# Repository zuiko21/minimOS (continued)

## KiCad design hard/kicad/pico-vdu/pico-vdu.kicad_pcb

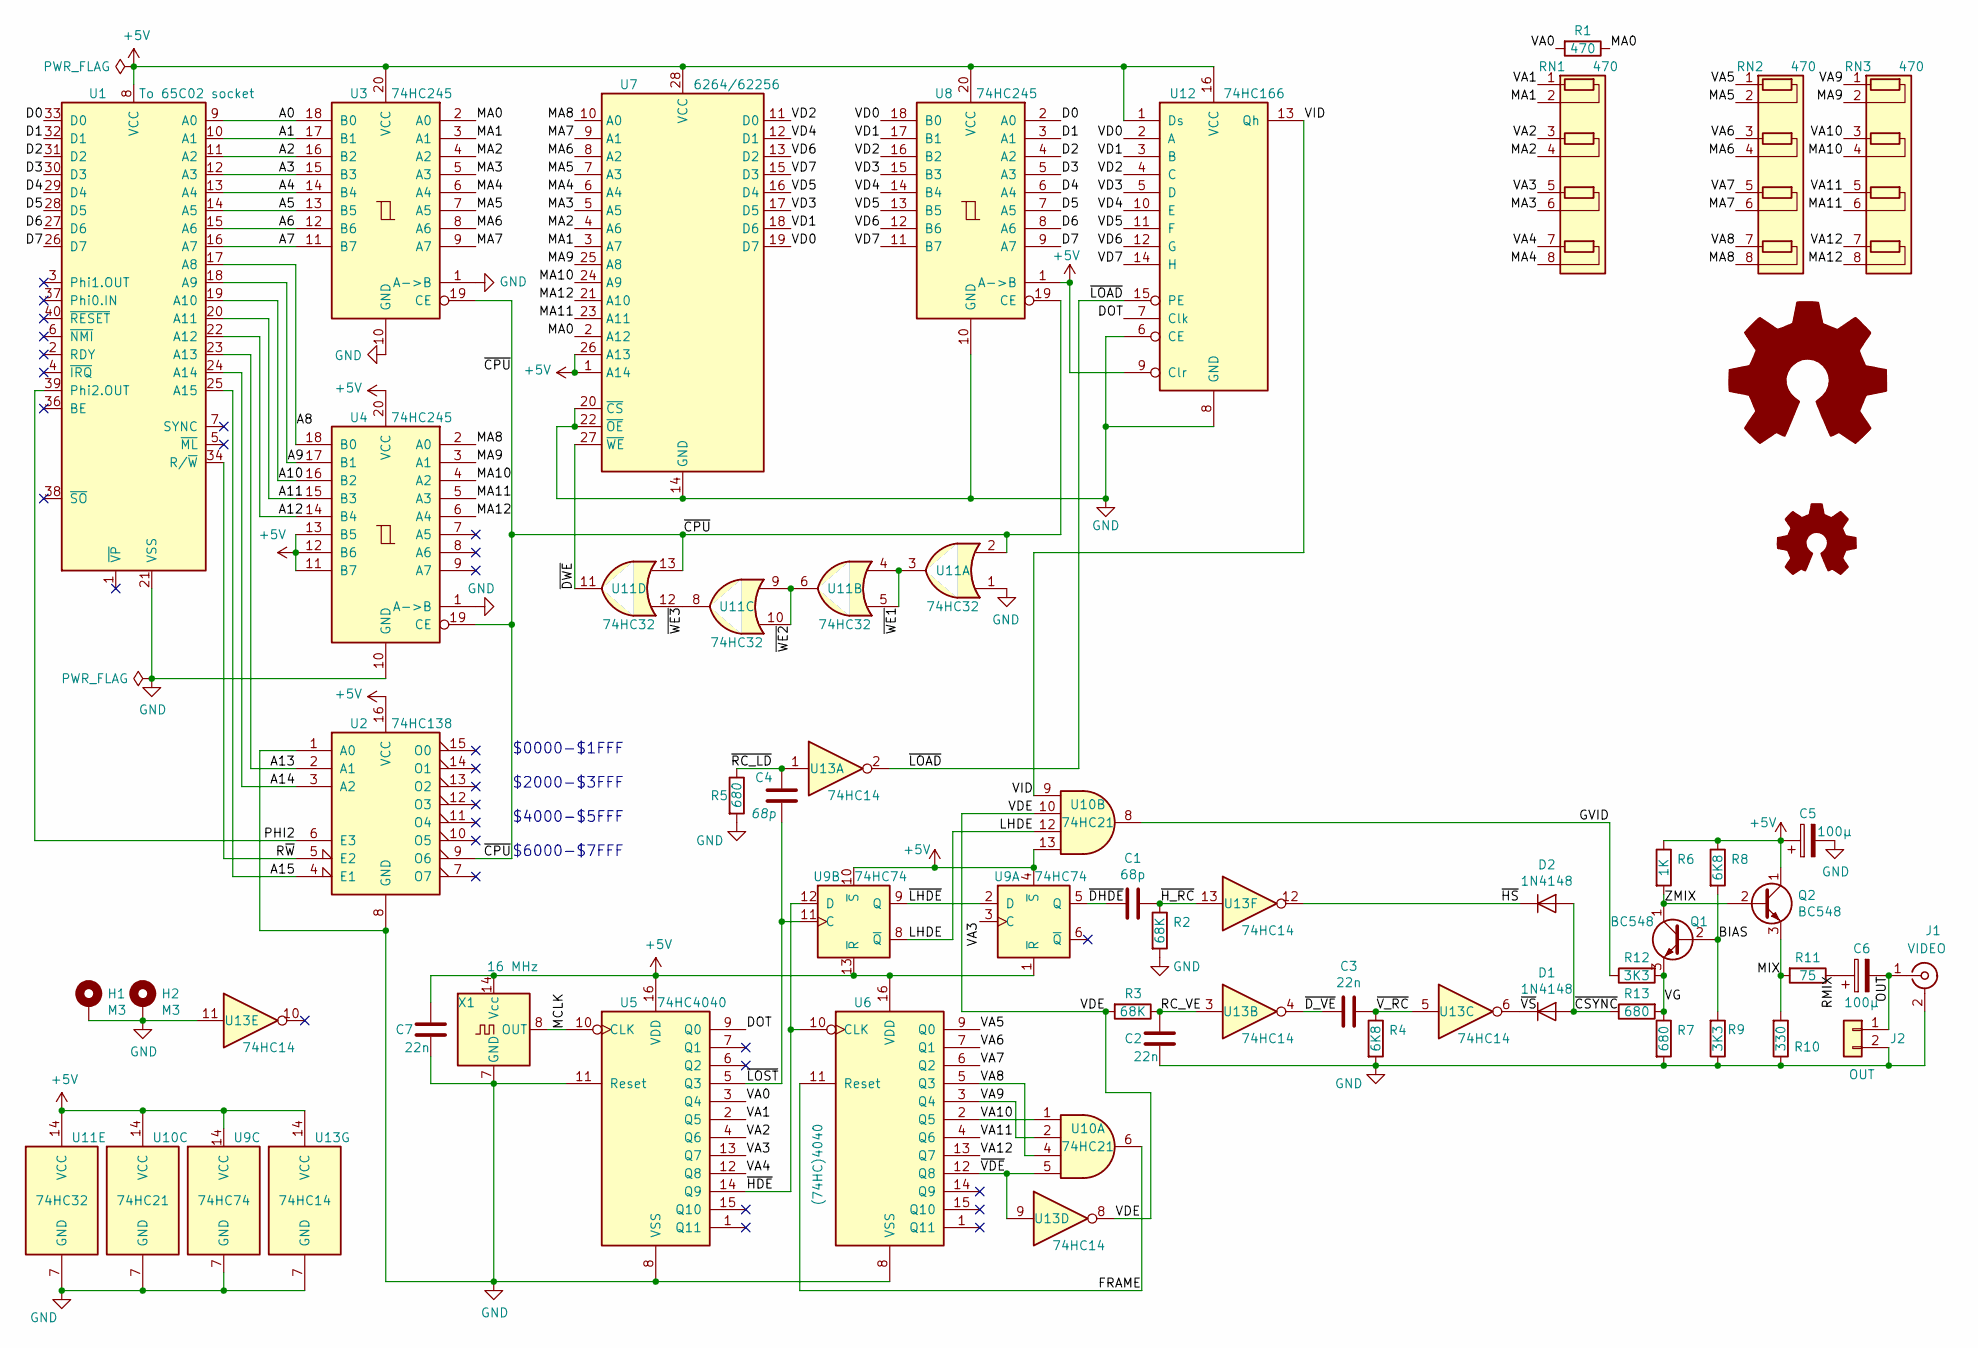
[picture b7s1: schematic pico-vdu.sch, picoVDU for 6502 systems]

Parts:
C1, C4: 68p; C_Disc_D3.8mm_W2.6mm_P2.50mm
C2, C3, C7: 22n; C_Rect_L7.2mm_W2.5mm_P5.00mm_FKS2_FKP2_MKS2_MKP2
C5, C6: 100µ; CP_Radial_D4.0mm_P1.50mm
D1, D2: 1N4148; D_DO-35_SOD27_P2.54mm_Vertical_AnodeUp
H1, H2: M3; MountingHole_3.2mm_M3_DIN965_Pad
J1: VIDEO; 1xRCA
J2: OUT; PinSocket_1x02_P2.54mm_Horizontal
LOGO1: Logo_Open_Hardware_Large; OSHW-Symbol_8.9x8mm_SilkScreen
LOGO2: La Jaquería; jaqueria
Q1, Q2: BC548; TO-92_Inline
R1: 470; R_Axial_DIN0207_L6.3mm_D2.5mm_P2.54mm_Vertical
R2, R3: 68K; R_Axial_DIN0207_L6.3mm_D2.5mm_P2.54mm_Vertical
R4, R8: 6K8; R_Axial_DIN0207_L6.3mm_D2.5mm_P2.54mm_Vertical
R5, R7, R13: 680; R_Axial_DIN0207_L6.3mm_D2.5mm_P2.54mm_Vertical
R6: 1K; R_Axial_DIN0207_L6.3mm_D2.5mm_P2.54mm_Vertical
R9, R12: 3K3; R_Axial_DIN0207_L6.3mm_D2.5mm_P2.54mm_Vertical
R10: 330; R_Axial_DIN0207_L6.3mm_D2.5mm_P2.54mm_Vertical
R11: 75; R_Axial_DIN0207_L6.3mm_D2.5mm_P2.54mm_Vertical
RN1, RN2, RN3: 470; R_Array_SIP8
U1: To 65C02 socket; DIP-40_W15.24mm_Socket
U2: 74HC138; DIP-16_W7.62mm_Socket
U3, U4, U8: 74HC245; DIP-20_W7.62mm_Socket
U5: 74HC4040; DIP-16_W7.62mm_Socket
U6: (74HC)4040; DIP-16_W7.62mm_Socket
U7: 6264/62256; DIP-28_W15.24mm_Socket
U9: 74HC74; DIP-14_W7.62mm_Socket
U10: 74HC21; DIP-14_W7.62mm_Socket
U11: 74HC32; DIP-14_W7.62mm_Socket
U12: 74HC166; DIP-16_W7.62mm_Socket
U13: 74HC14; DIP-14_W7.62mm_Socket
X1: 16 MHz; Oscillator_DIP-14

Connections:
+5V: C5.1, C7.2, Q2.1 (C), R6.1, R8.1, U1.8 (VCC), U2.16 (VCC), U3.20 (VCC), U4.11 (B7), U4.12 (B6), U4.13 (B5), U4.20 (VCC), U5.16 (VDD), U6.16 (VDD), U7.1 (A14), U7.26 (A13), U7.28 (VCC), U8.1 (A->B), U8.20 (VCC), U9.1 (~R), U9.4 (~S), U9.10 (~S), U9.13 (~R), U9.14 (VCC), U10.13, U10.14 (VCC), U11.14 (VCC), U12.1 (Ds), U12.9 (Clr), U12.16 (VCC), U13.14 (VCC), X1.14 (Vcc)
/A0: U1.9 (A0), U3.18 (B0)
/A1: U1.10 (A1), U3.17 (B1)
/A2: U1.11 (A2), U3.16 (B2)
/A3: U1.12 (A3), U3.15 (B3)
/A4: U1.13 (A4), U3.14 (B4)
/A5: U1.14 (A5), U3.13 (B5)
/A6: U1.15 (A6), U3.12 (B6)
/A7: U1.16 (A7), U3.11 (B7)
/A8: U1.17 (A8), U4.18 (B0)
/A9: U1.18 (A9), U4.17 (B1)
/A10: U1.19 (A10), U4.16 (B2)
/A11: U1.20 (A11), U4.15 (B3)
/A12: U1.22 (A12), U4.14 (B4)
/A13: U1.23 (A13), U2.2 (A1)
/A14: U1.24 (A14), U2.3 (A2)
/A15: U1.25 (A15), U2.4 (E1)
/BIAS: Q1.2 (B), R8.2, R9.2
/D0: U1.33 (D0), U8.2 (A0)
/D1: U1.32 (D1), U8.3 (A1)
/D2: U1.31 (D2), U8.4 (A2)
/D3: U1.30 (D3), U8.5 (A3)
/D4: U1.29 (D4), U8.6 (A4)
/D5: U1.28 (D5), U8.7 (A5)
/D6: U1.27 (D6), U8.8 (A6)
/D7: U1.26 (D7), U8.9 (A7)
/DOT: U5.9 (Q0), U12.7 (Clk)
/FRAME: U6.11 (Reset), U10.6
/GVID: R12.1, U10.8
/LHDE: U9.8 (~Q), U10.12
/MA0: R1.1, U3.2 (A0), U7.2 (A12)
/MA1: RN1.2 (R1.2), U3.3 (A1), U7.3 (A7)
/MA2: RN1.4 (R2.2), U3.4 (A2), U7.4 (A6)
/MA3: RN1.6 (R3.2), U3.5 (A3), U7.5 (A5)
/MA4: RN1.8 (R4.2), U3.6 (A4), U7.6 (A4)
/MA5: RN2.2 (R1.2), U3.7 (A5), U7.7 (A3)
/MA6: RN2.4 (R2.2), U3.8 (A6), U7.8 (A2)
/MA7: RN2.6 (R3.2), U3.9 (A7), U7.9 (A1)
/MA8: RN2.8 (R4.2), U4.2 (A0), U7.10 (A0)
/MA9: RN3.2 (R1.2), U4.3 (A1), U7.25 (A8)
/MA10: RN3.4 (R2.2), U4.4 (A2), U7.24 (A9)
/MA11: RN3.6 (R3.2), U4.5 (A3), U7.23 (A11)
/MA12: RN3.8 (R4.2), U4.6 (A4), U7.21 (A10)
/MCLK: U5.10 (CLK), X1.8 (OUT)
/MIX: Q2.3 (E), R10.2, R11.2
/OUT: C6.2, J1.1 (In), J2.1
/PHI2: U1.39 (Phi2.OUT), U2.6 (E3)
/RC_VE: C2.2, R3.1, U13.3
/RMIX: C6.1, R11.1
/R~W: U1.34 (R/~W), U2.5 (E2)
/VA0: R1.2, U5.3 (Q4)
/VA1: RN1.1 (R1.1), U5.2 (Q5)
/VA2: RN1.3 (R2.1), U5.4 (Q6)
/VA3: RN1.5 (R3.1), U5.13 (Q7), U9.3 (C)
/VA4: RN1.7 (R4.1), U5.12 (Q8)
/VA5: RN2.1 (R1.1), U6.9 (Q0)
/VA6: RN2.3 (R2.1), U6.7 (Q1)
/VA7: RN2.5 (R3.1), U6.6 (Q2)
/VA8: RN2.7 (R4.1), U6.5 (Q3), U10.4
/VA9: RN3.1 (R1.1), U6.3 (Q4), U10.2
/VA10: RN3.3 (R2.1), U6.2 (Q5), U10.1
/VA11: RN3.5 (R3.1), U6.4 (Q6)
/VA12: RN3.7 (R4.1), U6.13 (Q7)
/VD0: U7.19 (D7), U8.18 (B0), U12.2 (A)
/VD1: U7.18 (D6), U8.17 (B1), U12.3 (B)
/VD2: U7.11 (D0), U8.16 (B2), U12.4 (C)
/VD3: U7.17 (D5), U8.15 (B3), U12.5 (D)
/VD4: U7.12 (D1), U8.14 (B4), U12.10 (E)
/VD5: U7.16 (D4), U8.13 (B5), U12.11 (F)
/VD6: U7.13 (D2), U8.12 (B6), U12.12 (G)
/VD7: U7.15 (D3), U8.11 (B7), U12.14 (H)
/VDE: R3.2, U10.10, U13.8
/VG: Q1.3 (E), R7.1, R12.2, R13.2
/VID: U10.9, U12.13 (Qh)
/ZMIX: Q1.1 (C), Q2.2 (B), R6.2
/~CPU: U2.9 (O6), U3.19 (CE), U4.19 (CE), U8.19 (CE), U11.2, U11.13
/~CSYNC: D1.2 (A), D2.2 (A), R13.1
/~DHDE: C1.2, U9.5 (Q)
/~DWE: U7.27 (~WE~), U11.11
/~D_VE: C3.2, U13.4
/~HDE: U5.14 (Q9), U6.10 (CLK), U9.12 (D)
/~HS: D2.1 (K), U13.12
/~H_RC: C1.1, R2.1, U13.13
/~LHDE: U9.2 (D), U9.9 (Q)
/~LOAD: U12.15 (PE), U13.2
/~LOST: C4.1, U5.5 (Q3), U9.11 (C)
/~RC_LD: C4.2, R5.1, U13.1
/~VDE: U6.12 (Q8), U10.5, U13.9
/~VS: D1.1 (K), U13.6
/~V_RC: C3.1, R4.1, U13.5
/~WE1: U11.3, U11.4, U11.5
/~WE2: U11.6, U11.9, U11.10
/~WE3: U11.8, U11.12
GND: C2.1, C5.2, C7.1, H1.1, H2.1, J1.2 (Ext), J2.2, R2.2, R4.2, R5.2, R7.2, R9.1, R10.1, U1.21 (VSS), U2.1 (A0), U2.8 (GND), U3.1 (A->B), U3.10 (GND), U4.1 (A->B), U4.10 (GND), U5.8 (VSS), U5.11 (Reset), U6.8 (VSS), U7.14 (GND), U7.20 (~CS), U7.22 (~OE~), U8.10 (GND), U9.7 (GND), U10.7 (GND), U11.1, U11.7 (GND), U12.6 (CE), U12.8 (GND), U13.7 (GND), U13.11, X1.7 (GND)

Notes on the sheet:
$0000-$1FFF $2000-$3FFF $4000-$5FFF $6000-$7FFF

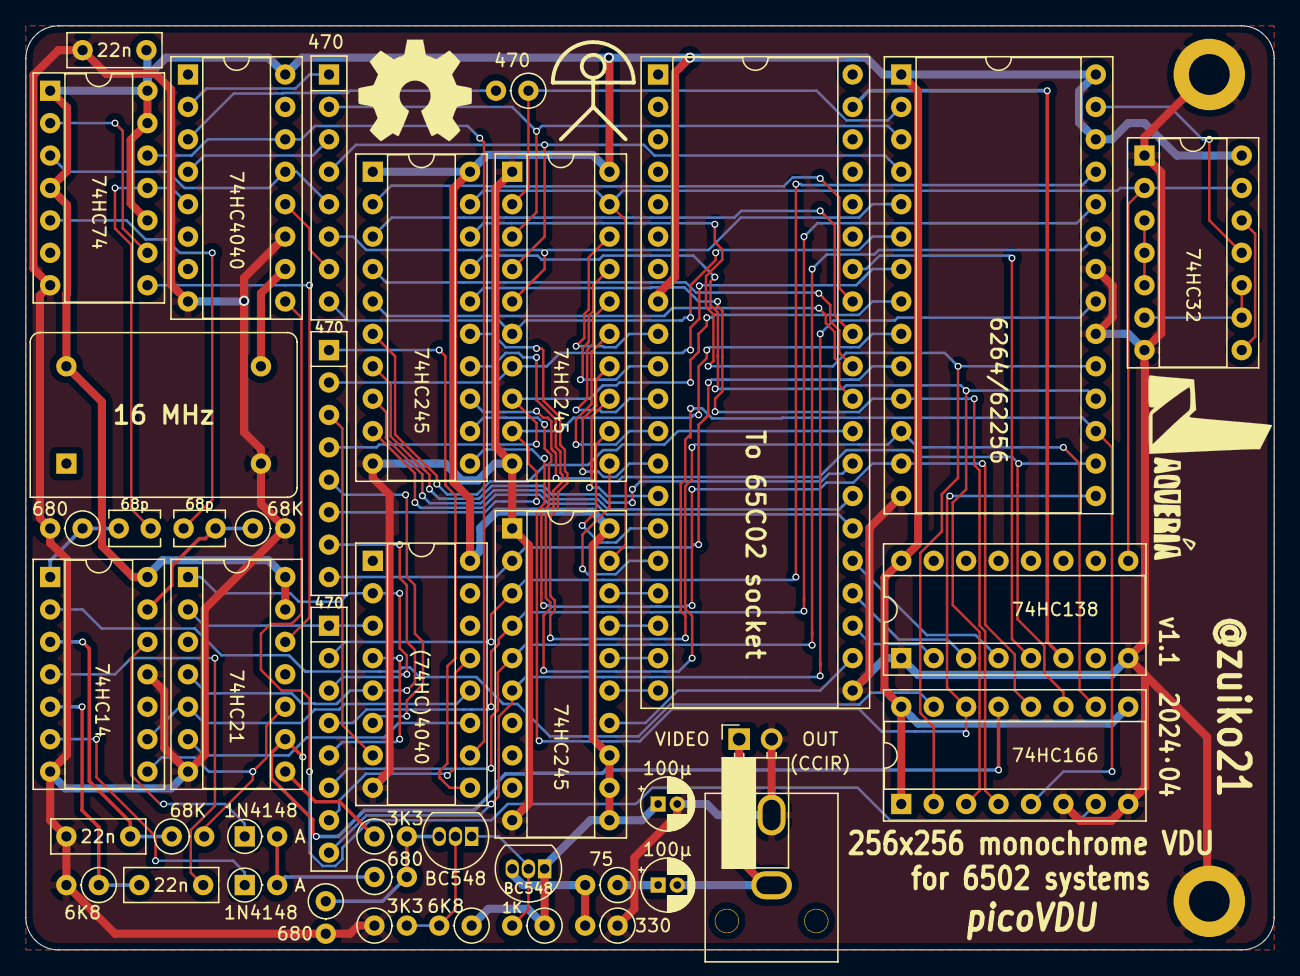
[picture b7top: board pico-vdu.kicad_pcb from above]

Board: 2 copper layers, 97.8 x 72.4 mm, 47 parts (0 on the bottom side), 94 nets.

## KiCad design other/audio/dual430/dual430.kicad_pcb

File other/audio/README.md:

This folder has NOTHING to do with **minimOS**, just a handy location for other 
projects.

*All rights reserved! (C) 2018-2020 Carlos J. Santisteban Salinas*

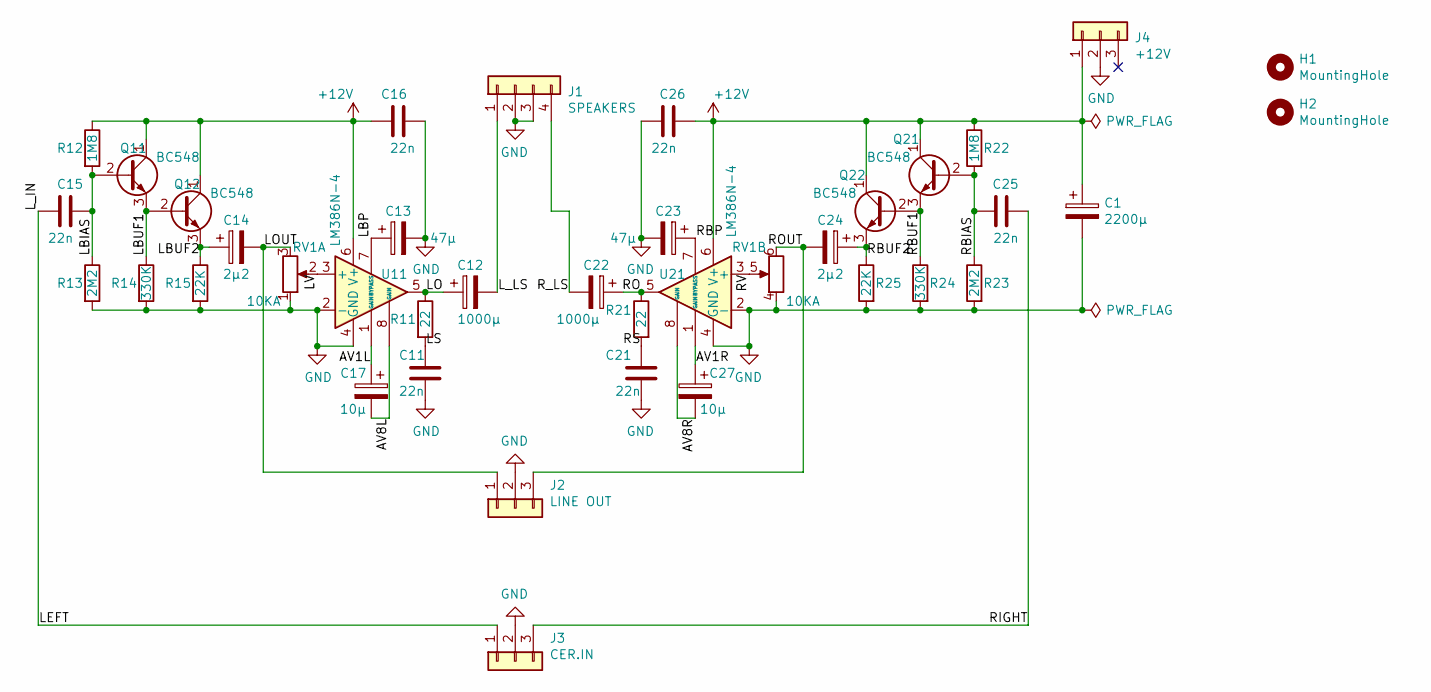
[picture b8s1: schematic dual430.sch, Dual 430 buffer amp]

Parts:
C1: 2200µ; CP_Radial_D13.0mm_P5.00mm
C11, C15, C16, C21, C25, C26: 22n; C_Rect_L7.0mm_W2.0mm_P5.00mm
C12, C22: 1000µ; CP_Radial_D10.0mm_P5.00mm
C13, C23: 47µ; CP_Radial_D4.0mm_P1.50mm
C14, C24: 2µ2; CP_Radial_D4.0mm_P1.50mm
C17, C27: 10µ; CP_Radial_D4.0mm_P1.50mm
H1, H2: MountingHole; MountingHole_3.2mm_M3_DIN965
J1: SPEAKERS; PinHeader_1x04_P2.54mm_Vertical
J2: LINE OUT; PinHeader_1x03_P2.54mm_Vertical
J3: CER.IN; PinHeader_1x03_P2.54mm_Vertical
J4: +12V; PinHeader_1x03_P2.54mm_Vertical
Q11, Q12, Q21, Q22: BC548; TO-92_Inline
R11, R21: 22; R_Axial_DIN0207_L6.3mm_D2.5mm_P10.16mm_Horizontal
R12, R22: 1M8; R_Axial_DIN0207_L6.3mm_D2.5mm_P10.16mm_Horizontal
R13, R23: 2M2; R_Axial_DIN0207_L6.3mm_D2.5mm_P10.16mm_Horizontal
R14, R24: 330K; R_Axial_DIN0207_L6.3mm_D2.5mm_P10.16mm_Horizontal
R15, R25: 22K; R_Axial_DIN0207_L6.3mm_D2.5mm_P10.16mm_Horizontal
RV1: 10KA; Potentiometer_Alps_225G_Dual_Horizontal
U11, U21: LM386N-4; DIP-8_W7.62mm_Socket

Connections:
+12V: C1.1, C16.2, C26.2, J4.1, Q11.1 (C), Q12.1 (C), Q21.1 (C), Q22.1 (C), R12.1, R22.1, U11.6 (V+), U21.6 (V+)
/AV1L: C17.1, U11.1 (GAIN)
/AV1R: C27.1, U21.1 (GAIN)
/AV8L: C17.2, U11.8 (GAIN)
/AV8R: C27.2, U21.8 (GAIN)
/LBIAS: C15.1, Q11.2 (B), R12.2, R13.1
/LBP: C13.1, U11.7 (BYPASS)
/LBUF1: Q11.3 (E), Q12.2 (B), R14.1
/LBUF2: C14.1, Q12.3 (E), R15.1
/LEFT: C15.2, J3.1
/LO: C12.1, R11.1, U11.5
/LOUT: C14.2, J2.1, RV1.3
/LS: C11.1, R11.2
/LV: RV1.2, U11.3 (+)
/L_LS: C12.2, J1.1
/RBIAS: C25.1, Q21.2 (B), R22.2, R23.1
/RBP: C23.1, U21.7 (BYPASS)
/RBUF1: Q21.3 (E), Q22.2 (B), R24.1
/RBUF2: C24.1, Q22.3 (E), R25.1
/RIGHT: C25.2, J3.3
/RO: C22.1, R21.1, U21.5
/ROUT: C24.2, J2.3, RV1.6
/RS: C21.1, R21.2
/RV: RV1.5, U21.3 (+)
/R_LS: C22.2, J1.4
GND: C1.2, C11.2, C13.2, C16.1, C21.2, C23.2, C26.1, J1.2, J1.3, J2.2, J3.2, J4.2, R13.2, R14.2, R15.2, R23.2, R24.2, R25.2, RV1.1, RV1.4, U11.2 (-), U11.4 (GND), U21.2 (-), U21.4 (GND)

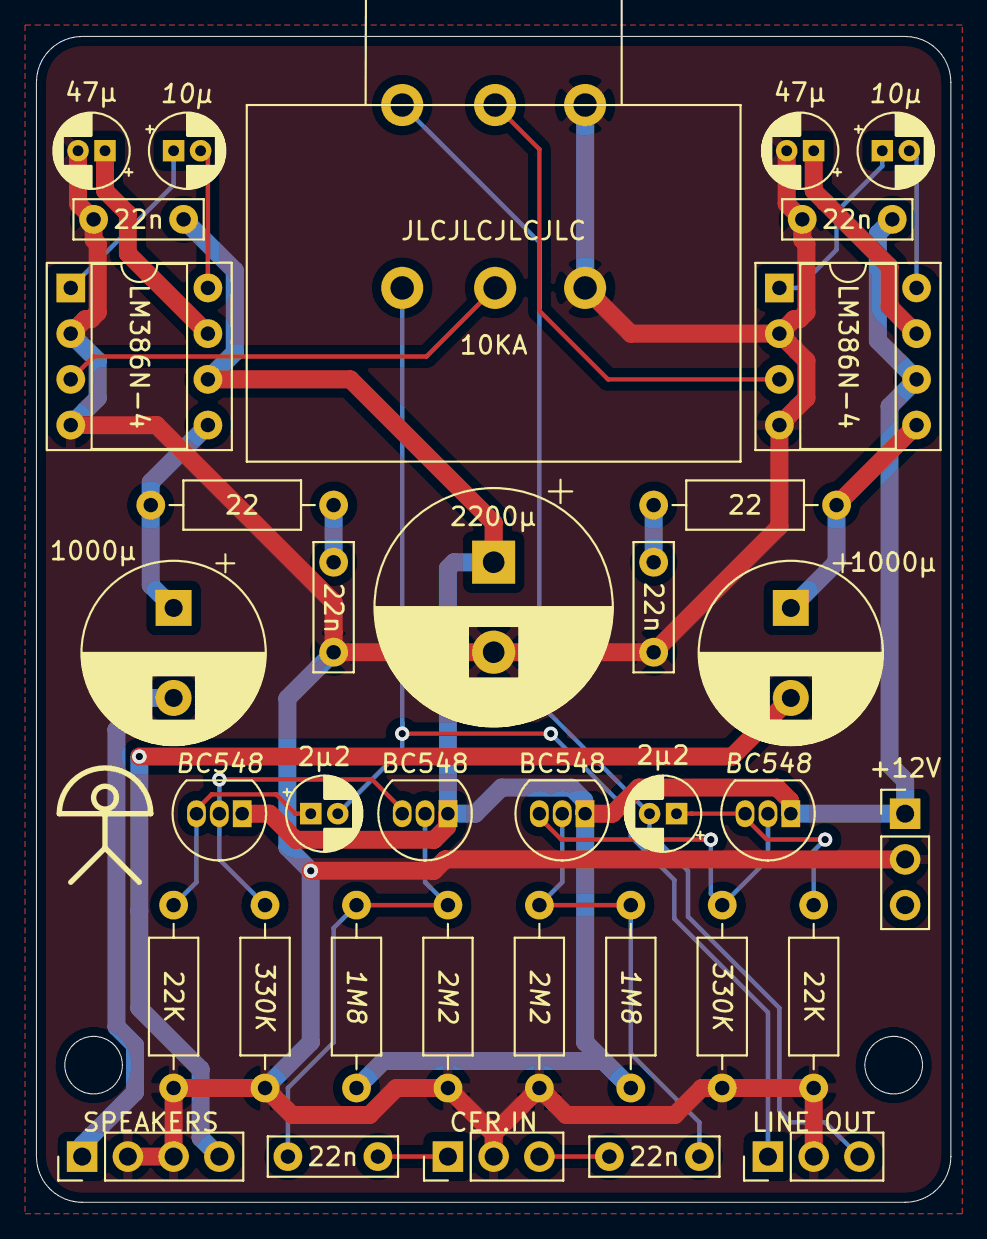
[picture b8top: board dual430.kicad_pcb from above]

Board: 2 copper layers, 50.8 x 64.8 mm, 38 parts (0 on the bottom side), 26 nets.

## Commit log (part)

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2024-05-14 use parameter for ppm2sv
2024-05-14 test demo
2024-05-14 test NMI
2024-05-14 fix NMI preset in demo
2024-05-14 glitch test
2024-05-15 way improved glitching
2024-05-15 some work on twister
2024-05-15 back to ISO 8859-1
2024-05-15 faster glitching
2024-05-15 shift and twist
2024-05-17 add PAL/NTSC encoder
2024-05-17 preliminary PAL/NTSC encoder layout
2024-05-22 add stub for Chihuahua test
2024-05-23 hard panic and ROM footer for Chihuahua test
2024-05-23 init VIA and add ISR plus panic
2024-05-25 add BASIC and CONIO for Chihuahua/picoVDU
2024-05-26 stub for Chihuahua components
2024-05-26 BASIC ready for Durango except BEEP
2024-05-26 5x8 driver ready for Chihuahua
2024-05-27 BEL for Chihuahua CONIO
2024-05-27 working on Chihuahua BEEP
2024-05-27 recode Chihuahua BASIC
2024-05-28 assemble test on MacMini
2024-05-28 stub for Chihuahua test sound
2024-05-30 insert music values
2024-06-05 add debug LEDs to Chihuahua test
2024-06-05 fix DEBUG and universal VIA access
2024-06-07 fix Chihuahua test
2024-06-08 NMI test and bong for Chihuahua test
2024-06-08 work on Chihuahua test
2024-06-08 fix stack bug on Chihuahua test
2024-06-08 patch to skip IRQ test
2024-06-10 recombina Chihuahua test
2024-06-10 remove IRQ test patch
2024-06-10 shut off PB7 t ggle
2024-06-11 safer bong config
2024-06-13 fix memory test
2024-06-13 attempt to fix Chihuahua test
2024-06-14 safer map probing, set ACR before SR
2024-06-18 make standalone nanoBoot Chihuahua compatible, fix init
2024-06-19 debug Chihuahua test at 328
2024-06-20 fix RAM mirroring for POCKET
2024-06-20 remove debug code, shorter envelope
2024-06-26 make bootloader Chihuahua-savvy
2024-06-26 minor fixes
2024-07-07 stub for plasma effect
2024-07-07 add definitions to plasma stub
2024-07-07 complete plasma for testing
2024-07-07 fix odd-sized Pocket on multiloader
2024-07-08 argument-based nanoBoot server
2024-07-08 safer parsing
2024-07-08 add debug code
2024-07-08 move debug code
2024-07-08 evaluate before
2024-07-16 add speed factor
2024-07-16 move RPi nanoBoot variables for fixed feedback
2024-07-16 fixed RasPi module feedback
2024-07-29 fix include in columns
2024-07-29 try to clear older column
2024-07-29 try faster update
2024-07-29 fix jewel redraw
2024-07-29 try progressive drop
2024-07-29 piece drop seems OK
2024-07-30 cleanup
2024-07-30 fix field2 initialisation
2024-07-30 fix proper player initialisation
2024-07-30 game end attempt
2024-07-30 alternative attempt does not work either
2024-07-30 fix death, but not as expected
2024-07-31 now dies accordingly
2024-07-31 try fixing when left kept
2024-07-31 fix lateral lock
2024-07-31 change flip index and fix lockup
2024-07-31 remove chkroom nonsense
2024-08-01 try further optimisation
2024-08-01 stub for horizontal match detection
2024-08-01 big refactor
2024-08-01 some cleanup, still bad init
2024-08-04 fix some indices
2024-08-06 locks at first drop (pl2 only)
2024-08-07 add pocket compatibility, still check
2024-08-07 fix pocket format
2024-08-07 remove check for testing
2024-08-11 add new stati
2024-08-11 fix status change
2024-08-11 simple peñonazo sound
2024-08-12 some cleanup, remove magic numbers
2024-08-12 shorter peñonazo sound
2024-08-12 detect magic jewel drop
2024-08-13 remove top magic tile for testing
2024-08-13 test proper detection of magic tiles
2024-08-13 for testing, clear detected tile under magic
2024-08-13 proper disposal of removed tiles
2024-08-13 blink attempt
2024-08-14 sort of viable columns
2024-08-14 deletes magic jewel temporarily
2024-08-14 try less frantic magic update
2024-08-14 failed to make less frantic magic update
2024-08-14 successful explosion
2024-08-15 awful attempt of tile drop
2024-08-16 fix drop loops
2024-08-16 very broken
2024-08-16 make global some temps improves a bit
2024-08-16 reposition LDX when generating, works again
2024-08-16 worse if I add player on drop vars
2024-08-16 DROP mostly operative
2024-08-16 add some delay between drop columns
2024-08-16 quick obvious bugs fix
2024-08-17 remove most of magic numbers
2024-08-17 forgot bytes per raster
2024-08-17 try blinking magic jewel upon crash
2024-08-17 magic blink failed
2024-08-17 simpler attempt to blink magic jewel
2024-08-17 attempt to detect horiz matches
2024-08-17 some horizontal matches detected
2024-08-18 fix obvious off-by-one
2024-08-18 add note to fix DROP
2024-08-18 rethread drop algorithm
2024-08-19 really fixed DROP
2024-08-20 failed attempt to add CHK sub-stati
2024-08-20 make room for new states
2024-08-20 reposition HCHK code
2024-08-20 ready for multithreaded checks
2024-08-21 fix trivial errors
2024-08-21 attempt for vertical matching
2024-08-21 vertical match working OK
2024-08-21 move do_match
2024-08-21 traps for match count
2024-08-21 update initial score
2024-08-21 fix BCD setting
2024-08-22 attempt for slash diagonals
2024-08-22 slash diagonals seem OK
2024-08-22 attempt for backslash diagonals
2024-08-22 fix constant, basic play OK
2024-08-23 try fixing uncleared top tiles
2024-08-23 some corruption on player 1 during player 2 use
2024-08-23 fix header
2024-08-23 test for corrupted select
2024-08-23 control index
2024-08-23 no idea
2024-08-23 fix IO overlap, still fails
2024-08-24 more checks, resets padmask
2024-08-24 fix improper index EEEEEEK
2024-08-24 reposition cl_mark calls, ready for cycle count
2024-08-24 attempt to count jewels
2024-08-24 jewel counter working
2024-08-24 try auto level change
2024-08-24 update speed according to level
2024-08-24 speed fix, ready for sound effect
2024-08-24 remove excessive sound effect
2024-08-25 try again sound effect
2024-08-25 switch to finer granularity
2024-08-25 adjust time constants for finer granularity
2024-08-25 proper event update
2024-08-25 provisional horizontal score
2024-08-25 fix horizontal score
2024-08-25 provisional score in all directions
2024-08-25 fix IO, score works minus magic
2024-08-26 test score overflow
2024-08-26 even more initial points
2024-08-26 magic jewel score attempt
2024-08-26 level test
2024-08-26 fix obvious multiply error, take hojalete factor
2024-08-26 checkpoint on bcd2bin
2024-08-26 seems bin2bcd is bad
2024-08-27 integrate addscore into bin2bcd
2024-08-27 add drop extra points
2024-08-27 functional (if ugly) pause
2024-08-27 placeholder for pause banner
2024-08-27 complete pause minus banner art
2024-08-27 add pause banner
2024-08-27 try pause banner
2024-08-27 first test
2024-08-27 RC1 test with improved pause
2024-08-27 BROKEN
2024-08-27 working but buggy
2024-08-28 full Columns RC1 working
2024-08-31 move Columns to own repository
2024-08-31 update links to new columns
2024-09-01 stub for sound player
2024-09-01 unify noise channel, stub for envelope
2024-09-02 unify tone and envelope loops
2024-09-02 rename, non-zero initial attack, fix sustain
2024-09-02 improve PSG delays
2024-09-03 test code for PSG sound manager
2024-09-03 new locals
2024-09-03 more local init
2024-09-03 experiments with psg test code
2024-09-03 redone volume changes
2024-09-03 full sg init
2024-09-03 try fixing overflow comparisons
2024-09-03 fix PSG controller daemon
2024-09-03 fix assembler errors in PSG player
2024-09-04 slight score reader optimisation
2024-09-04 try noise score
2024-09-04 rhythm works
2024-09-04 noise plays, melody just delays or crashes
2024-09-04 fix variable corruption on psg player
2024-09-04 fixed desynch
2024-09-04 256-tick note OK, attack envelope bad
2024-09-04 minimal opt for PSG player
2024-09-05 fix current volume mask
2024-09-05 test some fixes
2024-09-05 envelopes check out ok
2024-09-08 fix first note muted
2024-09-08 add variable ZP pointer location
2024-09-08 move memory allocation for easier reset
2024-09-09 upscaled score
2024-09-13 add envelope test
2024-09-13 envelope updates
2024-09-14 try drums
2024-09-14 experiment with noise channel
2024-09-15 fix columns tempo
2024-09-16 optimised note conversion for TURBO
2024-09-16 set turbo mode
2024-09-19 add 4t delays after PSG access
2024-09-19 safe delays
2024-09-21 add extended keyboard test
2024-09-21 improve extended keyboard test
2024-09-24 add RND test
2024-09-24 fix RNG test init
2024-09-24 add random pixel test
2024-09-26 combine probs and pixel randomness test
2024-09-26 configurable rnd test
2024-09-26 test linear prng
2024-09-26 fix tmp and try magic numbers
2024-09-27 Randomness tester in JS
2024-10-01 add test for ShadowRAM
2024-10-01 add DurangoPLUS compatibility on bootloader
2024-10-01 32K shadowRAM test
2024-10-01 add stub for integrity test
2024-10-02 improve integrity test
2024-10-03 fix JMPs to half-page tests
2024-10-03 stub for specific header and init checksums
2024-10-03 complete init test minus checksum values
2024-10-03 complete partial tests
2024-10-03 add partial checksum values
2024-10-03 improve partial test display
2024-10-04 fix Chihuahua feedback on ROM images
2024-10-05 remove whole IO page from integrity test
2024-10-05 short test before IO
2024-10-05 failed attempt of universal boot
2024-10-05 completely universal bootloader
2024-10-08 stub for I2C transfer
2024-10-09 stub for virtual Durango
2024-10-10 improved stack frame and NZ check
2024-10-10 some more 6502 opcodes virtualised
2024-10-11 attempt for alternative BIT emulation
2024-10-11 extensive use of _BYTE macro
2024-10-11 attempt for relative branch emulation
2024-10-14 some work on I2C
2024-10-15 ad clock stretching with timeout
2024-10-16 fix timing and code surrounding I2C
2024-10-17 add test IO code
2024-10-17 fix BRK and IO
2024-10-17 some NACK support
2024-10-17 optimise print
2024-10-17 some work
2024-10-18 proper RTC addressing and data gathering
2024-10-19 complete interface for I2C test
2024-10-19 ready for I2C test
2024-10-19 complete I2C test
2024-10-19 arb error, disabled still no good
2024-10-19 read byte from I2C properly
2024-10-19 fix initial bitbang, still bad
2024-10-21 fix data read after NAK
2024-10-21 no restart condition
2024-10-24 try alternative I2C algorithm
2024-10-24 improve 24h RTC display
2024-10-25 improme reset and AM/PM display
2024-10-29 stub for cat's eye computation
2024-10-29 add unrouted RTC+SPI sidecar
2024-10-29 minor IC placement
2024-10-30 minor passive repositioning
2024-10-31 recode and some fixing on catseye.bas
2024-11-01 sidecar fully routed
2024-11-03 add some silkscreen to RTC/SD sidecar
2024-11-10 add stub for PLUS keyboard
2024-11-11 add stub for OMRON keyboard
2024-11-12 finish stub for OMRON keyboard
2024-11-21 cross dron board
2024-11-23 update dron
2024-11-23 update dron with slots
2024-11-24 complete motor holes for dron
2024-11-24 add limits to rtc-sd
2024-11-24 reduce axle hole
2024-11-28 add tri-PSG
2024-11-28 cleanup and final triPSG opt
2024-11-28 12 pads to enroute for triPSG
2024-11-30 fully enrouted triPSG
2024-12-01 fix silcreen on triPSG, ready for order
2024-12-19 PCM player for TriPSG
2024-12-21 handle LED on PCM player
2024-12-21 complete PCM player
2024-12-22 low-Z values for TriPSG
2025-03-21 fix bootloader and vertical 2xRCA
2025-03-25 stub for CLI parameter-based imager
2025-03-25 new function prototypes
2025-03-25 suggest parameters for function calls in main
2025-03-25 Updated open volume function
2025-03-25 Updated add-to-volume function
2025-03-26 Updated extract and set free space
2025-03-26 defined error codes
2025-03-26 rehandling most errors
2025-03-27 refactor comments
2025-03-27 attempt for executable main code
2025-03-28 generic result string info()
2025-04-02 stub for modifying code in volume handling
2025-04-03 dirty parameter parsing
2025-04-08 supposedly complete parsing on imager
2025-04-10 fix output volume, still rejects makeshift end-of-volume
2025-04-11 fix imager file handling, remove fake end-of-volume but allow bad header
2025-04-23 removing global state
2025-04-23 remove attempt of global status, still bad prototypes
2025-04-24 remove global status completed
2025-04-24 Do not delete image when empty
2025-04-24 fix and some refactor
2025-04-24 add debug code to deletion
2025-04-24 more debug code
2025-04-24 fix deletion error, remove dabug code
2025-04-25 add extraction path
2025-04-25 Update version number
2025-04-25 improve help screen
2025-04-25 separate interface for ID/name based extraction/deletion
2025-04-25 preliminary support for ID-based extraction/deletion
2025-04-25 fix case
2025-04-25 imager checked OK
2025-05-23 stub for pacmanR.s
